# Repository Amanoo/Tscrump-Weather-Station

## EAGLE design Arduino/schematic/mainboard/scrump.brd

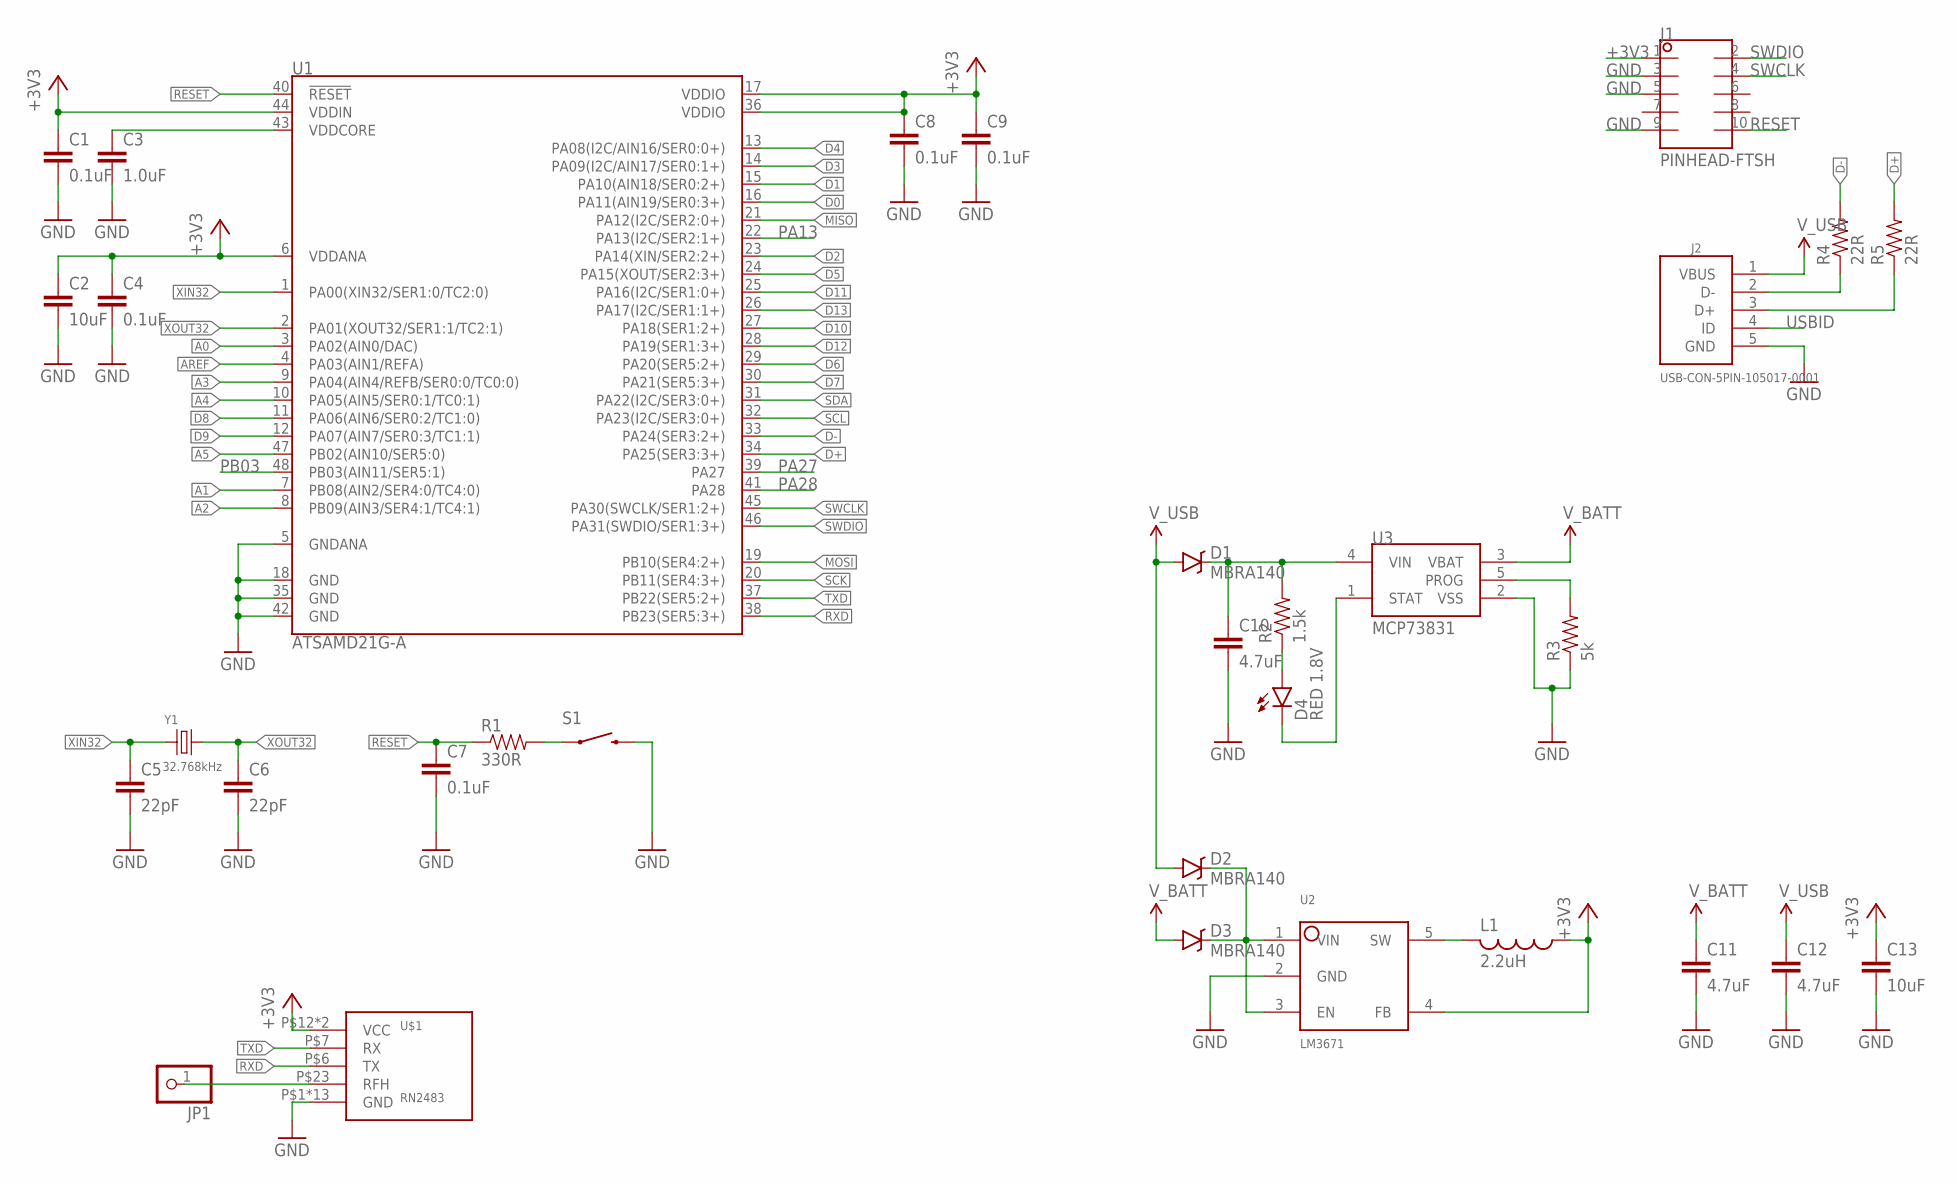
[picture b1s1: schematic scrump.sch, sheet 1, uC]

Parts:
C1, C4, C7, C8, C9: 0.1uF; 0603-CAP
C2, C13: 10uF; 0603-CAP
C3: 1.0uF; 0603-CAP
C5, C6: 22pF; 0603-CAP
C10, C11, C12: 4.7uF; 0603-CAP
D1, D2, D3: MBRA140; SMA-DIODE
D4: RED 1.8V; LED-0603
J1: PINHEAD-FTSH; FTSH-105-01-XXX-DV-K
J2: USB-CON-5PIN-105017-0001; USB-MICRO-MOLEX-105017-0001
JP1: PINHD-1X1; 1X01
L1: 2.2uH; 0806-INDUCTOR
R1: 330R; 0603-RES
R2: 1.5k; 0603-RES
R3: 5k; 0603-RES
R4, R5: 22R; 0603-RES
S1: PUSHBUTTON-SMD; TACTILE-SMD-SWITCH
U1: ATSAMD21G-A; TQFP-48
U2: LM3671; SOT23-5
U3: MCP73831; SOT23-5
U$1: RN2483
Y1: 32.768kHz; ABS25

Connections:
+3V3: C1.1, C2.1, C4.1, C8.1, C9.1, C13.1, J1.1, L1.1, U1.6 (VDDANA), U1.17 (VDDIO), U1.36 (VDDIO), U1.44 (VDDIN), U2.4 (FB), U$1.P$12 (VCC), U$1.P$34 (VCC); also elsewhere on the board
A0: U1.3 (PA02(AIN0/DAC)); also elsewhere on the board
A1: U1.7 (PB08(AIN2/SER4:0/TC4:0))
A2: U1.8 (PB09(AIN3/SER4:1/TC4:1))
A3: U1.9 (PA04(AIN4/REFB/SER0:0/TC0:0))
A4: U1.10 (PA05(AIN5/SER0:1/TC0:1))
A5: U1.47 (PB02(AIN10/SER5:0))
AREF: U1.4 (PA03(AIN1/REFA))
D0: U1.16 (PA11(AIN19/SER0:3+))
D1: U1.15 (PA10(AIN18/SER0:2+))
D2: U1.23 (PA14(XIN/SER2:2+))
D3: U1.14 (PA09(I2C/AIN17/SER0:1+))
D4: U1.13 (PA08(I2C/AIN16/SER0:0+)); also elsewhere on the board
D5: U1.24 (PA15(XOUT/SER2:3+))
D6: U1.29 (PA20(SER5:2+))
D7: U1.30 (PA21(SER5:3+))
D8: U1.11 (PA06(AIN6/SER0:2/TC1:0))
D9: U1.12 (PA07(AIN7/SER0:3/TC1:1))
D10: U1.27 (PA18(SER1:2+))
D11: U1.25 (PA16(I2C/SER1:0+))
D12: U1.28 (PA19(SER1:3+))
D13: U1.26 (PA17(I2C/SER1:1+))
D+: R5.2, U1.34 (PA25(SER3:3+))
D-: R4.2, U1.33 (PA24(SER3:2+))
GND: C1.2, C2.2, C3.2, C4.2, C5.2, C6.2, C7.2, C8.2, C9.2, C10.2, C11.2, C12.2, C13.2, J1.3, J1.5, J1.9, J2.5 (GND), R3.1, S1.P$3 (2), S1.P$4 (2), U1.5 (GNDANA), U1.18 (GND), U1.35 (GND), U1.42 (GND), U2.2 (GND), U3.2 (VSS), U$1.P$1 (GND), U$1.P$8 (GND), U$1.P$11 (GND), U$1.P$20 (GND), U$1.P$21 (GND), U$1.P$22 (GND), U$1.P$24 (GND), U$1.P$26 (GND), U$1.P$27 (GND), U$1.P$28 (GND), U$1.P$33 (GND), U$1.P$41 (GND), U$1.P$47 (GND); also elsewhere on the board
MISO: U1.21 (PA12(I2C/SER2:0+))
MOSI: U1.19 (PB10(SER4:2+))
unnamed: C3.1, U1.43 (VDDCORE)
unnamed: R1.2, S1.P$1 (1), S1.P$2 (1)
unnamed: C10.1, D1.C, R2.2, U3.4 (VIN)
unnamed: J2.3 (D+), R5.1
unnamed: L1.2, U2.5 (SW)
unnamed: D4.C, U3.1 (STAT)
unnamed: D4.A, R2.1
unnamed: R3.2, U3.5 (PROG)
unnamed: J2.2 (D-), R4.1
unnamed: D2.C, D3.C, U2.1 (VIN), U2.3 (EN)
unnamed: JP1.1, U$1.P$23 (RFH)
PA13: U1.22 (PA13(I2C/SER2:1+))
PA27: U1.39 (PA27)
PA28: U1.41 (PA28)
PB03: U1.48 (PB03(AIN11/SER5:1))
RESET: C7.1, J1.10, R1.1, U1.40 (!RESET!)
RXD: U1.38 (PB23(SER5:3+)), U$1.P$6 (TX)
SCK: U1.20 (PB11(SER4:3+))
SCL: U1.32 (PA23(I2C/SER3:0+)); also elsewhere on the board
SDA: U1.31 (PA22(I2C/SER3:0+)); also elsewhere on the board
SWCLK: J1.4, U1.45 (PA30(SWCLK/SER1:2+))
SWDIO: J1.2, U1.46 (PA31(SWDIO/SER1:3+))
TXD: U1.37 (PB22(SER5:2+)), U$1.P$7 (RX)
USBID: J2.4 (ID)
V_BATT: C11.1, D3.A, U3.3 (VBAT)
V_USB: C12.1, D1.A, D2.A, J2.1 (VBUS)
XIN32: C5.1, U1.1 (PA00(XIN32/SER1:0/TC2:0)), Y1.P$1 (1)
XOUT32: C6.1, U1.2 (PA01(XOUT32/SER1:1/TC2:1)), Y1.P$4 (3)

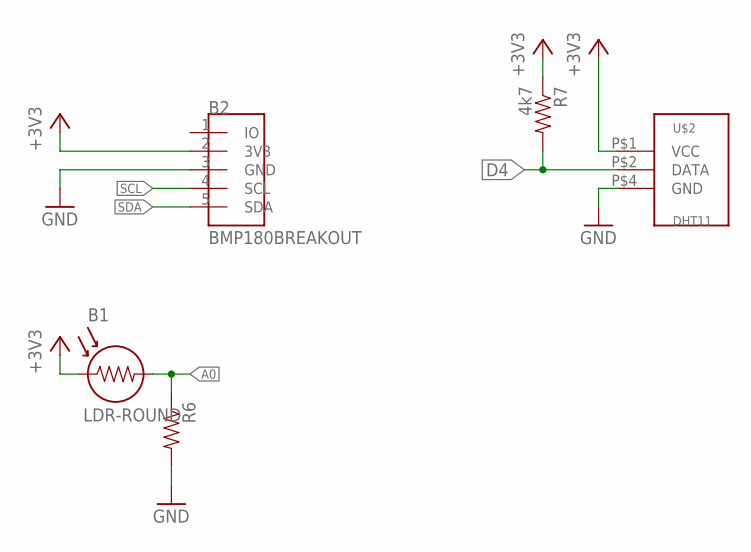
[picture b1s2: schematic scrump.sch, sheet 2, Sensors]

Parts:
B1: LDR-ROUND
B2: BMP180BREAKOUT; BMP180_BREAKOUT
R6: RESISTOR0603; 0603-RES
R7: 4k7; 0603-RES
U$2: DHT11

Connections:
+3V3: B1.P$1 (1), B2.2 (3V3), R7.1, U$2.P$1 (VCC); also elsewhere on the board
A0: B1.P$2 (2), R6.1; also elsewhere on the board
D4: R7.2, U$2.P$2 (DATA); also elsewhere on the board
GND: B2.3 (GND), R6.2, U$2.P$4 (GND); also elsewhere on the board
SCL: B2.4 (SCL); also elsewhere on the board
SDA: B2.5 (SDA); also elsewhere on the board

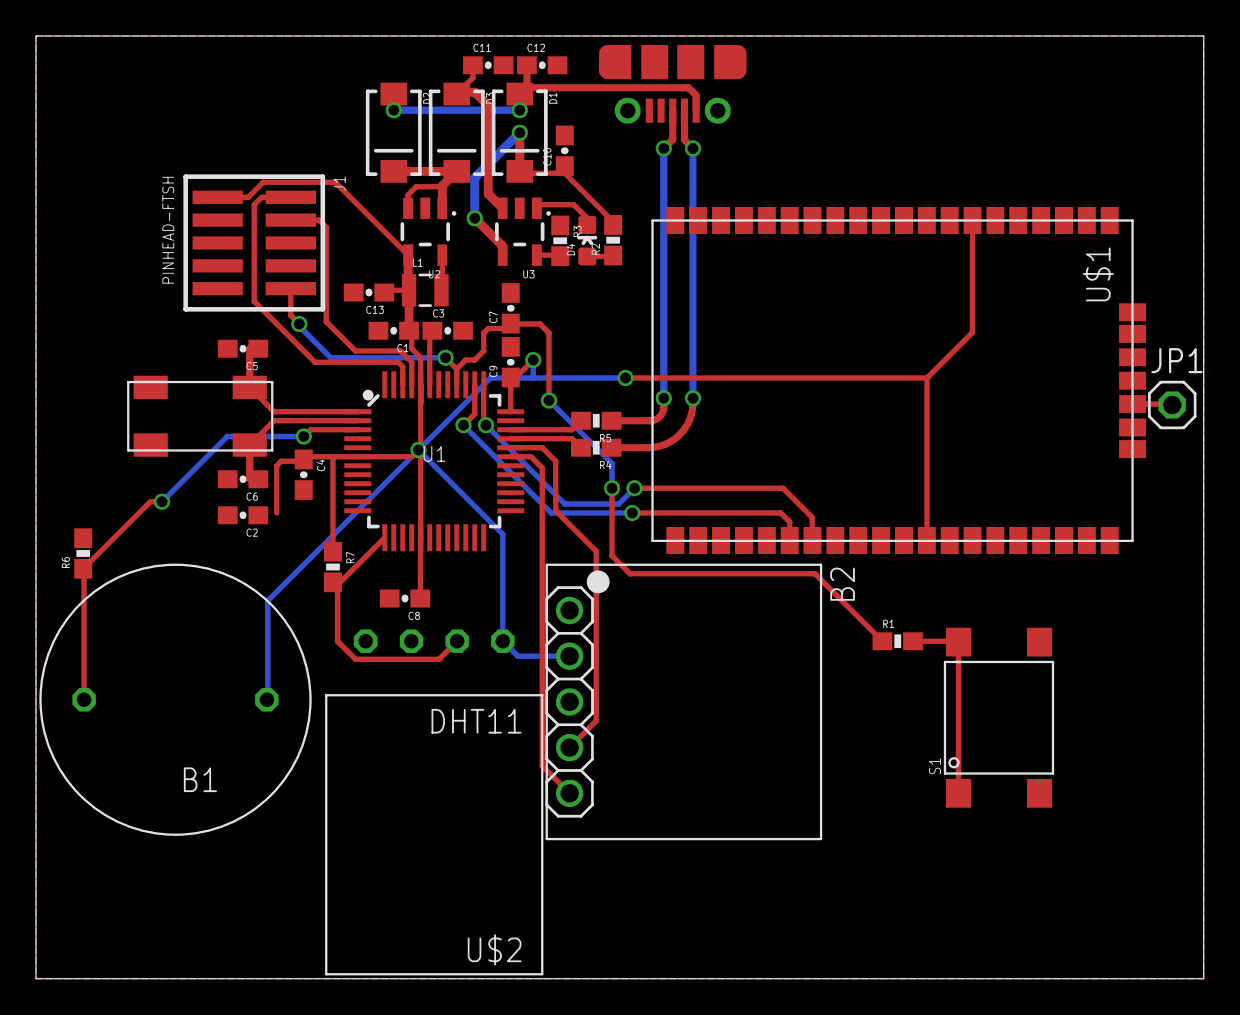
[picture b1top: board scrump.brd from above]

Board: 2 copper layers, 64.9 x 52.4 mm, 37 parts (0 on the bottom side), 28 nets.

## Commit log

2016-12-03 Initial PCB
2016-12-05 PCB changes
2016-12-05 Added LDR
2016-12-12 Finished initial version of PCB pending review

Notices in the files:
parts and their libraries:
SparkFun-Capacitors: Licensing: Creative Commons ShareAlike 4.0 International - https://creativecommons.org/licenses/by-sa/4.0
